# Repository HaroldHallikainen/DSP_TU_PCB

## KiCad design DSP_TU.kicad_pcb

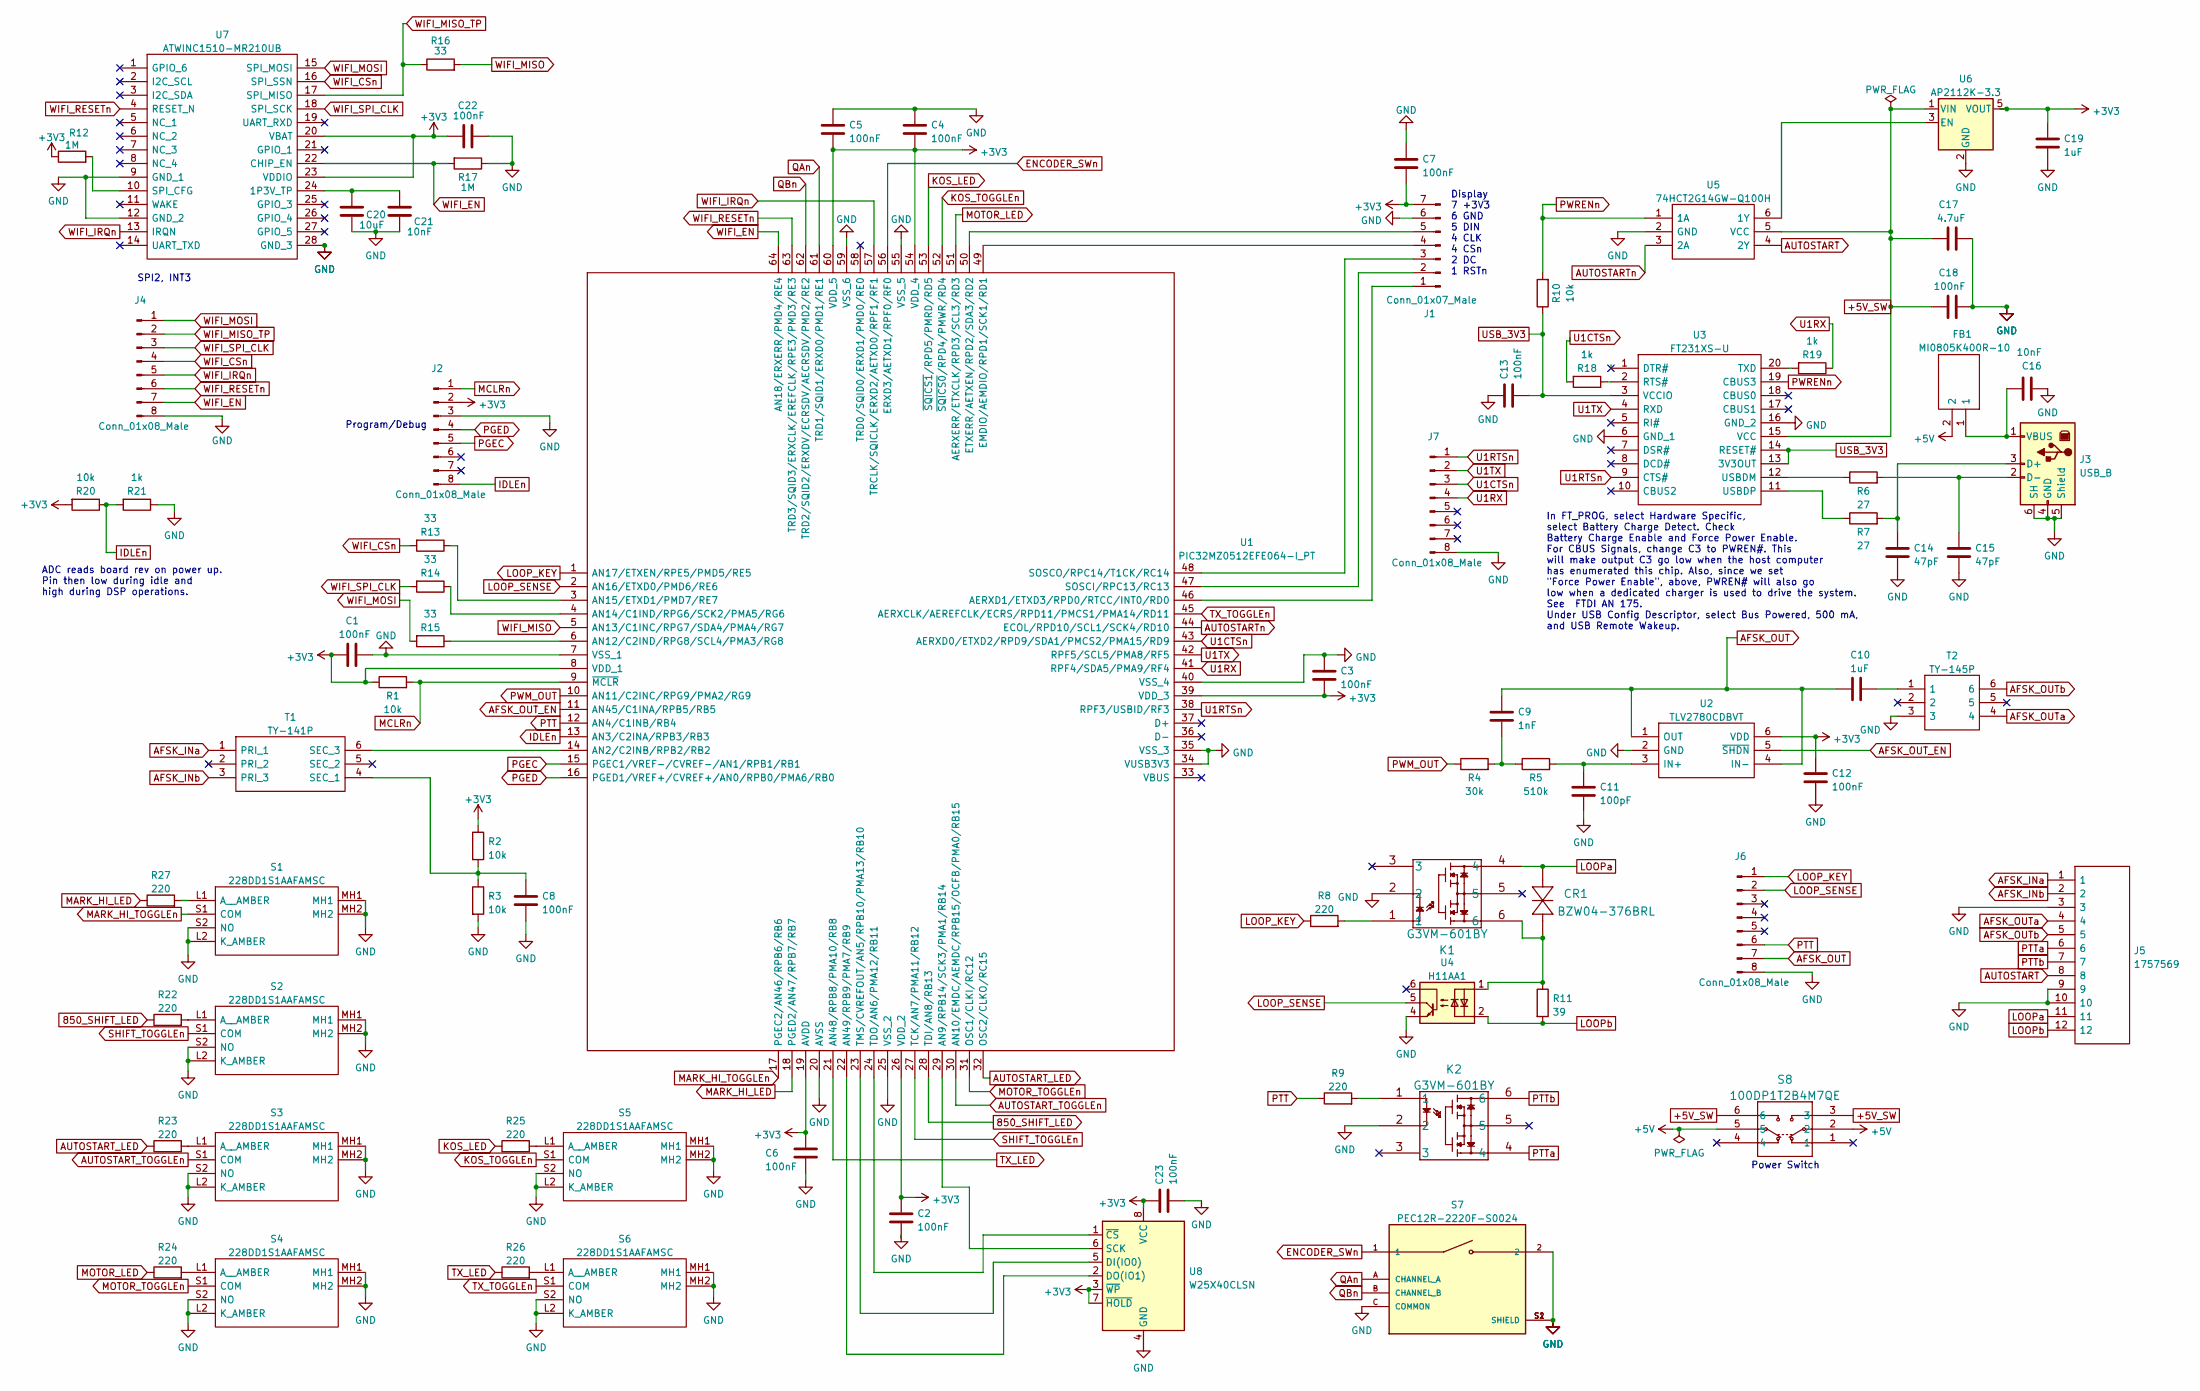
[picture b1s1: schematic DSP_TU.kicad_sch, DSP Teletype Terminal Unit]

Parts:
C1, C2, C3, C4, C5, C6, C7, C8, C12, C13, C18, C22, C23: 100nF; C_0603_1608Metric_Pad1.08x0.95mm_HandSolder
C9: 1nF; C_0603_1608Metric_Pad1.08x0.95mm_HandSolder
C10, C19: 1uF; C_0603_1608Metric_Pad1.08x0.95mm_HandSolder
C11: 100pF; C_0603_1608Metric_Pad1.08x0.95mm_HandSolder
C14, C15: 47pF; C_0603_1608Metric_Pad1.08x0.95mm_HandSolder
C16, C21: 10nF; C_0603_1608Metric_Pad1.08x0.95mm_HandSolder
C17: 4.7uF; C_0603_1608Metric_Pad1.08x0.95mm_HandSolder
C20: 10uF; C_0603_1608Metric_Pad1.08x0.95mm_HandSolder
CR1: BZW04-376BRL
FB1: MI0805K400R-10; BEADC2012X110N; Manufacturer_Part_Number MI0805K400R-10; Mouser Part Number 875-MI0805K400R-10
J1: Conn_01x07_Male; PinHeader_1x07_P2.54mm_Horizontal
J2, J4, J6, J7: Conn_01x08_Male; PinHeader_1x08_P2.54mm_Vertical
J3: USB_B; UJ2-BH-BL1-TH
J5: 1757569; Manufacturer_Part_Number 1757569; Mouser Part Number 651-1757569
K1, K2: G3VM-601BY; DIP-6_W7.62mm
R1, R2, R3, R10, R20: 10k; R_0603_1608Metric_Pad0.98x0.95mm_HandSolder
R4: 30k; R_0603_1608Metric_Pad0.98x0.95mm_HandSolder
R5: 510k; R_0603_1608Metric_Pad0.98x0.95mm_HandSolder
R6, R7: 27; R_0603_1608Metric_Pad0.98x0.95mm_HandSolder
R8, R9, R22, R23, R24, R25, R26, R27: 220; R_0603_1608Metric_Pad0.98x0.95mm_HandSolder
R11: 39; R_0603_1608Metric_Pad0.98x0.95mm_HandSolder
R12, R17: 1M; R_0603_1608Metric_Pad0.98x0.95mm_HandSolder
R13, R14, R15, R16: 33; R_0603_1608Metric_Pad0.98x0.95mm_HandSolder
R18, R19, R21: 1k; R_0603_1608Metric_Pad0.98x0.95mm_HandSolder
S1, S2, S3, S4, S5, S6: 228DD1S1AAFAMSC; Manufacturer_Part_Number 228DD1S1AAFAMSC; Mouser Part Number 774-228DD1S1AAFAMSC
S7: PEC12R-2220F-S0024; XDCR_PEC12R-2220F-S0024; PARTREV 07/21
S8: 100DP1T2B4M7QE; 100DP1T2B4M7QE_EWI
T1: TY-141P; DIPS1067W107P475L2062H1880Q6N; Manufacturer_Part_Number TY-141P; Mouser Part Number 553-TY141P
T2: TY-145P; DIPS1067W107P475L2062H1880Q6N; Manufacturer_Part_Number TY-145P; Mouser Part Number 553-TY145P
U1: PIC32MZ0512EFE064-I_PT; QFP50P1200X1200X120-64N; Manufacturer_Part_Number PIC32MZ0512EFE064-I/PT; Mouser Part Number 579-MZ0512EFE064IPT
U2: TLV2780CDBVT; SOT95P280X145-6N; Manufacturer_Part_Number TLV2780CDBVT; Mouser Part Number 595-TLV2780CDBVT
U3: FT231XS-U; SSOP-20_5.3x7.2mm_P0.65mm; Manufacturer_Part_Number FT231XS-U; Mouser Part Number 895-FT231XS-U
U4: H11AA1; DIP-6_W7.62mm
U5: 74HCT2G14GW-Q100H; 74HCT2G14GWQ100H; Manufacturer_Part_Number 74HCT2G14GW-Q100H; Mouser Part Number 771-74HCT2G14GWQ100H
U6: AP2112K-3.3; SOT-23-5
U7: ATWINC1510-MR210UB; ATWINC1510MR210UB; Mouser Part Number 556-ATWINC1510MR210U
U8: W25X40CLSN; SOIC-8_3.9x4.9mm_P1.27mm

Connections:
850_SHIFT_LED: R22.1, U1.28 (TDI/AN8/RB13)
+3V3: C1.2, C2.1, C3.2, C4.2, C5.2, C6.1, C7.2, C12.1, C19.1, C22.1, C23.1, J1.7, J2.2, R1.1, R2.1, R12.1, R20.2, U1.8 (VDD_1), U1.19 (AVDD), U1.26 (VDD_2), U1.39 (VDD_3), U1.54 (VDD_4), U1.60 (VDD_5), U2.6 (VDD), U6.5 (VOUT), U7.20 (VBAT), U7.23 (VDDIO), U8.3 (~WP), U8.7 (~HOLD), U8.8 (VCC)
+5V: FB1.2, S8.2, S8.5
+5V_SW: C17.1, C18.1, S8.3, S8.6, U3.15 (VCC), U5.5 (VCC), U6.1 (VIN)
AFSK_INa: J5.1, T1.1 (PRI_1)
AFSK_INb: J5.2, T1.3 (PRI_3)
AFSK_OUT: C9.1, C10.2, J6.7, U2.1 (OUT), U2.4 (IN-)
AFSK_OUT_EN: U1.11 (AN45/C1INA/RPB5/RB5), U2.5 (~SHDN)
AFSK_OUTa: J5.4, T2.4
AFSK_OUTb: J5.5, T2.6
AUTOSTART: J5.8, U5.4 (2Y)
AUTOSTART_LED: R23.1, U1.32 (OSC2/CLKO/RC15)
AUTOSTART_TOGGLEn: S3.S1 (COM), U1.30 (AN10/EMDC/AEMDC/RPB15/OCFB/PMA0/RB15)
AUTOSTARTn: U1.44 (ECOL/RPD10/SCL1/SCK4/RD10), U5.3 (2A)
ENCODER_SWn: S7.1, U1.56 (ERXD3/AETXD1/RPF0/RF0)
GND: C1.1, C2.2, C3.1, C4.1, C5.1, C6.2, C7.1, C8.2, C11.2, C12.2, C13.1, C14.2, C15.2, C16.2, C17.2, C18.2, C19.2, C20.2, C21.2, C22.2, C23.2, J1.6, J2.3, J3.4 (GND), J3.5 (Shield), J3.6 (SH), J4.8, J5.3, J5.9, J5.10, J6.8, J7.8, K1.2, K2.2, R3.2, R17.1, R21.1, S1.L2 (K_AMBER), S1.MH1, S1.MH2, S1.S2 (NO), S2.L2 (K_AMBER), S2.MH1, S2.MH2, S2.S2 (NO), S3.L2 (K_AMBER), S3.MH1, S3.MH2, S3.S2 (NO), S4.L2 (K_AMBER), S4.MH1, S4.MH2, S4.S2 (NO), S5.L2 (K_AMBER), S5.MH1, S5.MH2, S5.S2 (NO), S6.L2 (K_AMBER), S6.MH1, S6.MH2, S6.S2 (NO), S7.2, S7.C (COMMON), S7.S1 (SHIELD), S7.S2 (SHIELD), T2.3, U1.7 (VSS_1), U1.20 (AVSS), U1.25 (VSS_2), U1.34 (VUSB3V3), U1.35 (VSS_3), U1.40 (VSS_4), U1.55 (VSS_5), U1.59 (VSS_6), U2.2 (GND), U3.6 (GND_1), U3.16 (GND_2), U4.4, U5.2 (GND), U6.2 (GND), U7.9 (GND_1), U7.12 (GND_2), U7.28 (GND_3), U8.4 (GND)
IDLEn: J2.8, R20.1, R21.2, U1.13 (AN3/C2INA/RPB3/RB3)
KOS_LED: R25.1, U1.53 (~SQICS1/RPD5/PMRD/RD5)
KOS_TOGGLEn: S5.S1 (COM), U1.52 (~SQICS0/RPD4/PMWR/RD4)
LOOP_KEY: J6.1, R8.1, U1.1 (AN17/ETXEN/RPE5/PMD5/RE5)
LOOP_SENSE: J6.2, U1.2 (AN16/ETXD0/PMD6/RE6), U4.5
LOOPa: CR1.1 (CATHODE/ANODE), J5.11, K1.4
LOOPb: J5.12, R11.2, U4.2
MARK_HI_LED: R27.1, U1.18 (PGED2/AN47/RPB7/RB7)
MARK_HI_TOGGLEn: S1.S1 (COM), U1.17 (PGEC2/AN46/RPB6/RB6)
MCLRn: J2.1, R1.2, U1.9 (~MCLR)
MOTOR_LED: R24.1, U1.51 (AERXERR/ETXCLK/RPD3/SCL3/RD3)
MOTOR_TOGGLEn: S4.S1 (COM), U1.31 (OSC1/CLKI/RC12)
unnamed: C9.2, R4.2, R5.1
unnamed: C10.1, T2.1
unnamed: CR1.2 (CATHODE/ANODE), K1.6, R11.1, U4.1
unnamed: J1.1, U1.46 (AERXD1/ETXD3/RPD0/RTCC/INT0/RD0)
unnamed: J1.2, U1.47 (SOSCI/RPC13/RC13)
unnamed: J1.3, U1.48 (SOSCO/RPC14/T1CK/RC14)
unnamed: J1.4, U1.49 (EMDIO/AEMDIO/RPD1/SCK1/RD1)
unnamed: J1.5, U1.50 (ETXERR/AETXEN/RPD2/SDA3/RD2)
unnamed: C14.1, J3.3 (D+), R7.2
unnamed: C15.1, J3.2 (D-), R6.2
unnamed: C16.1, FB1.1, J3.1 (VBUS)
unnamed: K1.1, R8.2
unnamed: K2.1, R9.2
unnamed: R27.2, S1.L1 (A__AMBER)
unnamed: R22.2, S2.L1 (A__AMBER)
unnamed: R23.2, S3.L1 (A__AMBER)
unnamed: R24.2, S4.L1 (A__AMBER)
unnamed: R25.2, S5.L1 (A__AMBER)
unnamed: R26.2, S6.L1 (A__AMBER)
unnamed: C8.1, R2.2, R3.1, T1.4 (SEC_1)
unnamed: T1.6 (SEC_3), U1.14 (AN2/C2INB/RPB2/RB2)
unnamed: U1.29 (AN9/RPB14/SCK3/PMA1/RB14), U8.6 (SCK)
unnamed: R15.1, U1.6 (AN12/C2IND/RPG8/SCL4/PMA3/RG8)
unnamed: R14.1, U1.4 (AN14/C1IND/RPG6/SCK2/PMA5/RG6)
unnamed: R13.1, U1.3 (AN15/ETXD1/PMD7/RE7)
unnamed: U1.22 (AN49/RPB9/PMA7/RB9), U8.2 (DO(IO1))
unnamed: U1.24 (TDO/AN6/PMA12/RB11), U8.1 (~CS)
unnamed: U1.23 (TMS/CVREFOUT/AN5/RPB10/PMA13/RB10), U8.5 (DI(IO0))
unnamed: C11.1, R5.2, U2.3 (IN+)
unnamed: R18.1, U3.2 (RTS#)
unnamed: R19.2, U3.20 (TXD)
unnamed: R6.1, U3.12 (USBDM)
unnamed: R7.1, U3.11 (USBDP)
unnamed: U5.6 (1Y), U6.3 (EN)
unnamed: C20.1, C21.1, U7.24 (1P3V_TP)
unnamed: R12.2, U7.10 (SPI_CFG)
PGEC: J2.5, U1.15 (PGEC1/VREF-/CVREF-/AN1/RPB1/RB1)
PGED: J2.4, U1.16 (PGED1/VREF+/CVREF+/AN0/RPB0/PMA6/RB0)
PTT: J6.6, R9.1, U1.12 (AN4/C1INB/RB4)
PTTa: J5.6, K2.4
PTTb: J5.7, K2.6
PWM_OUT: R4.1, U1.10 (AN11/C2INC/RPG9/PMA2/RG9)
PWRENn: R10.2, U3.19 (CBUS3), U5.1 (1A)
QAn: S7.A (CHANNEL_A), U1.61 (TRD1/SQID1/ERXD0/PMD1/RE1)
QBn: S7.B (CHANNEL_B), U1.62 (TRD2/SQID2/ERXDV/ECRSDV/AECRSDV/PMD2/RE2)
SHIFT_TOGGLEn: S2.S1 (COM), U1.27 (TCK/AN7/PMA11/RB12)
TX_LED: R26.1, U1.21 (AN48/RPB8/PMA10/RB8)
TX_TOGGLEn: S6.S1 (COM), U1.45 (AERXCLK/AEREFCLK/ECRS/RPD11/PMCS1/PMA14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)
U1CTSn: J7.3, R18.2, U1.43 (AERXD0/ETXD2/RPD9/SDA1/PMCS2/PMA15/RD9)
U1RTSn: J7.1, U1.38 (RPF3/USBID/RF3), U3.9 (CTS#)
U1RX: J7.4, R19.1, U1.41 (RPF4/SDA5/PMA9/RF4)
U1TX: J7.2, U1.42 (RPF5/SCL5/PMA8/RF5), U3.4 (RXD)
USB_3V3: C13.2, R10.1, U3.3 (VCCIO), U3.13 (3V3OUT), U3.14 (RESET#)
WIFI_CSn: J4.4, R13.2, U7.16 (SPI_SSN)
WIFI_EN: J4.7, R17.2, U1.64 (AN18/ERXERR/PMD4/RE4), U7.22 (CHIP_EN)
WIFI_IRQn: J4.5, U1.57 (TRCLK/SQICLK/ERXD2/AETXD0/RPF1/RF1), U7.13 (IRQN)
WIFI_MISO: R16.2, U1.5 (AN13/C1INC/RPG7/SDA4/PMA4/RG7)
WIFI_MISO_TP: J4.2, R16.1, U7.17 (SPI_MISO)
WIFI_MOSI: J4.1, R15.2, U7.15 (SPI_MOSI)
WIFI_RESETn: J4.6, U1.63 (TRD3/SQID3/ERXCLK/EREFCLK/RPE3/PMD3/RE3), U7.4 (RESET_N)
WIFI_SPI_CLK: J4.3, R14.2, U7.18 (SPI_SCK)

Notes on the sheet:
Power Switch
SPI2, INT3
In FT_PROG, select Hardware Specific, select Battery Charge Detect. Check Battery Charge Enable and Force Power Enable. For CBUS Signals, change C3 to PWREN#. This will make output C3 go low when the host computer has enumerated this chip. Also, since we set "Force Power Enable", above, PWREN# will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
Display 7 +3V3 6 GND 5 DIN 4 CLK 4 CSn 2 DC 1 RSTn
ADC reads board rev on power up. Pin then low during idle and high during DSP operations.
Program/Debug

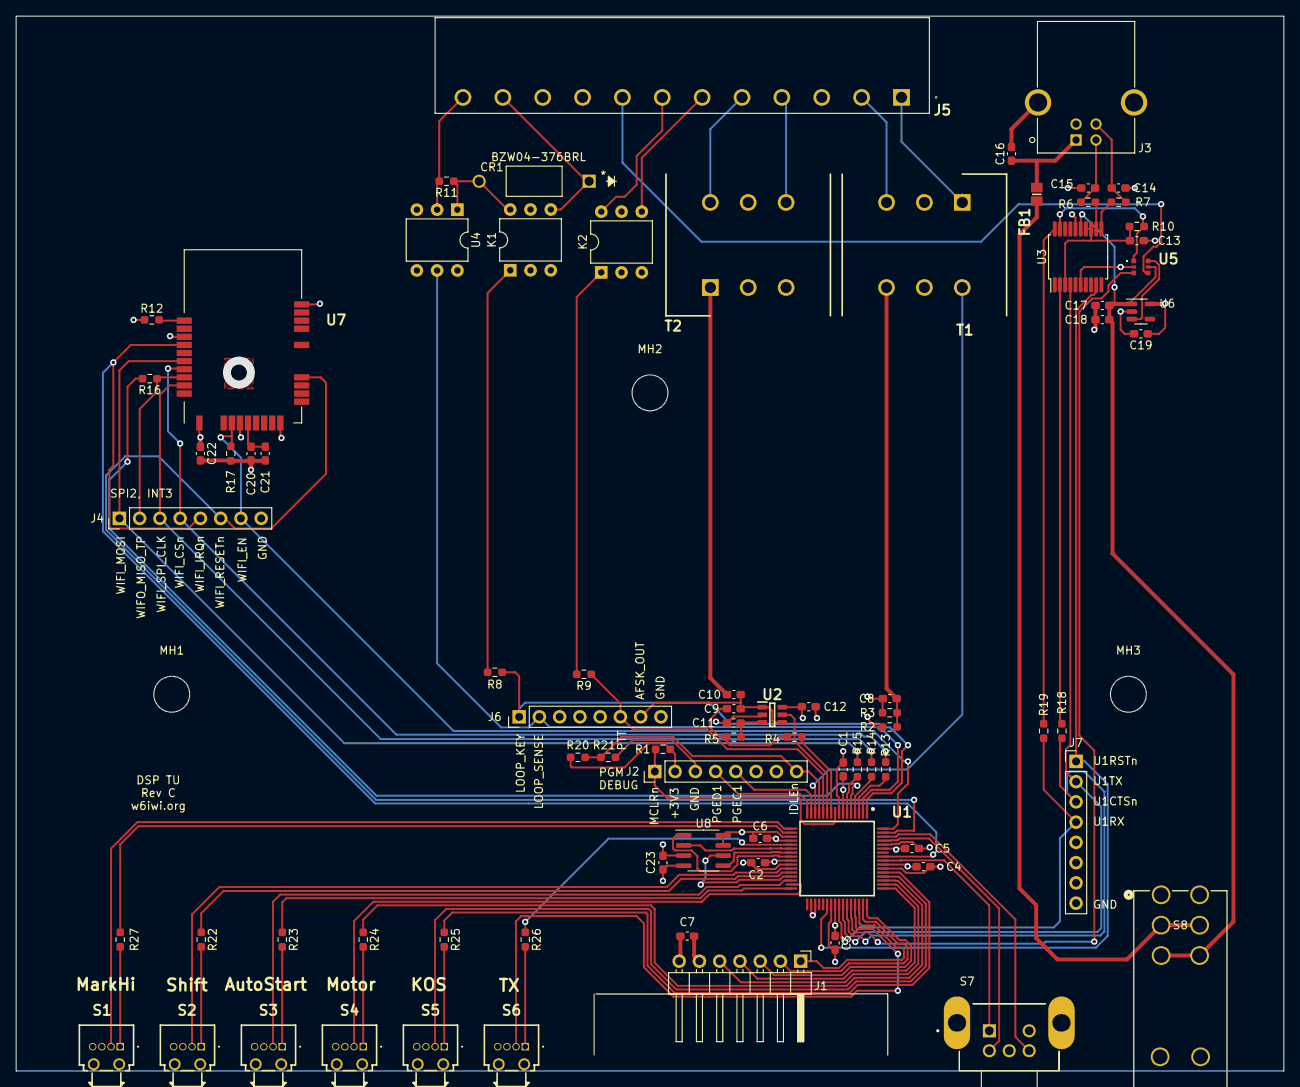
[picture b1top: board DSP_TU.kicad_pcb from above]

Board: 4 copper layers, 159.0 x 132.3 mm, 82 parts (0 on the bottom side), 89 nets.

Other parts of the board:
MH1, MH2, MH3: MountingHole_4.5mm

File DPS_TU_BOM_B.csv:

"Reference","Value","Datasheet","Footprint","Qty","DNP"
"C1,C2,C3,C4,C5,C6,C7,C8,C12,C13,C18,C22,C23","100nF","~","Capacitor_SMD:C_0603_1608Metric_Pad1.08x0.95mm_HandSolder","13",""
"C9","1nF","~","Capacitor_SMD:C_0603_1608Metric_Pad1.08x0.95mm_HandSolder","1",""
"C10,C19","1uF","~","Capacitor_SMD:C_0603_1608Metric_Pad1.08x0.95mm_HandSolder","2",""
"C11","100pF","~","Capacitor_SMD:C_0603_1608Metric_Pad1.08x0.95mm_HandSolder","1",""
"C14,C15","47pF","~","Capacitor_SMD:C_0603_1608Metric_Pad1.08x0.95mm_HandSolder","2",""
"C16,C21","10nF","~","Capacitor_SMD:C_0603_1608Metric_Pad1.08x0.95mm_HandSolder","2",""
"C17","4.7uF","~","Capacitor_SMD:C_0603_1608Metric_Pad1.08x0.95mm_HandSolder","1",""
"C20","10uF","~","Capacitor_SMD:C_0603_1608Metric_Pad1.08x0.95mm_HandSolder","1",""
"CR1","BZW04-376BRL","","HhLibrary:BZW04-376BRL","1",""
"FB1","MI0805K400R-10","https://assets.lairdtech.com/home/brandworld/files/MI0805K40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","HhLibrary:BEADC2012X110N","1",""
"J1","Conn_01x07_Male","~","Connector_PinHeader_2.54mm:PinHeader_1x07_P2.54mm_Horizontal","1",""
"J2,J4,J6,J7","Conn_01x08_Male","~","Connector_PinHeader_2.54mm:PinHeader_1x08_P2.54mm_Vertical","4",""
"J3","USB_B"," ~","HhLibrary:UJ2-BH-BL1-TH","1",""
"J5","1757569","http://www.phoenixcontact.com/de/produkte/1757569/pdf","HhLibrary:1757569","1",""
"K1,K2","G3VM-601BY","","Package_DIP:DIP-6_W7.62mm","2",""
"R1,R2,R3,R10,R20","10k","~","Resistor_SMD:R_0603_1608Metric_Pad0.98x0.95mm_HandSolder","5",""
"R4","30k","~","Resistor_SMD:R_0603_1608Metric_Pad0.98x0.95mm_HandSolder","1",""
"R5","510k","~","Resistor_SMD:R_0603_1608Metric_Pad0.98x0.95mm_HandSolder","1",""
"R6,R7","27","~","Resistor_SMD:R_0603_1608Metric_Pad0.98x0.95mm_HandSolder","2",""
"R8,R9,R22,R23,R24,R25,R26,R27","220","~","Resistor_SMD:R_0603_1608Metric_Pad0.98x0.95mm_HandSolder","8",""
"R11","39","~","Resistor_SMD:R_0603_1608Metric_Pad0.98x0.95mm_HandSolder","1",""
"R12,R17","1M","~","Resistor_SMD:R_0603_1608Metric_Pad0.98x0.95mm_HandSolder","2",""
"R13,R14,R15,R16","33","~","Resistor_SMD:R_0603_1608Metric_Pad0.98x0.95mm_HandSolder","4",""
"R18,R19,R21","1k","~","Resistor_SMD:R_0603_1608Metric_Pad0.98x0.95mm_HandSolder","3",""
"S1,S2,S3,S4,S5,S6","228DD1S1AAFAMSC","https://www.ctscorp.com/wp-content/uploads/228D.pdf","228DD1S1AAFAMSC","6",""
"S7","PEC12R-2220F-S0024","","XDCR_PEC12R-2220F-S0024","1",""
"S8","100DP1T2B4M7QE","100DP1T2B4M7QE","100DP1T2B4M7QE_EWI","1",""
"T1","TY-141P","http://catalog.triadmagnetics.com/Asset/TY-141P.pdf","HhLibrary:DIPS1067W107P475L2062H1880Q6N","1",""
"T2","TY-145P","https://catalog.triadmagnetics.com/Asset/TY-145P.pdf","HhLibrary:DIPS1067W107P475L2062H1880Q6N","1",""
"U1","PIC32MZ0512EFE064-I_PT","http://www.mouser.com/ds/2/268/60001320D-967555.pdf","HhLibrary:QFP50P1200X1200X120-64N","1",""
"U2","TLV2780CDBVT","https://www.ti.com/general/docs/suppproductinfo.tsp?distId=2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","HhLibrary:SOT95P280X145-6N","1",""
"U3","FT231XS-U","https://www.ftdichip.com/Support/Documents/DataSheets/ICs/DS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","Package_SO:SSOP-20_5.3x7.2mm_P0.65mm","1",""
"U4","H11AA1","https://www.vishay.com/docs/83608/h11aa1.pdf","Package_DIP:DIP-6_W7.62mm","1",""
"U5","74HCT2G14GW-Q100H","https://assets.nexperia.com/documents/data-sheet/74HC_HCT2G1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","HhLibrary:74HCT2G14GWQ100H","1",""
"U6","AP2112K-3.3","https://www.diodes.com/assets/Datasheets/AP2112.pdf","Package_TO_SOT_SMD:SOT-23-5","1",""
"U7","ATWINC1510-MR210UB","http://ww1.microchip.com/downloads/en/DeviceDoc/70005304B.pdf","HhLibrary:ATWINC1510MR210UB","1",""
"U8","W25X40CLSN","https://www.winbond.com/resource-files/W25X40CL_G%2020210505.pdf","Package_SO:SOIC-8_3.9x4.9mm_P1.27mm","1",""

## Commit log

2023-09-10 PCB rev A
2024-07-12 PCB Rev B, changing dimensions, adding test points, adding resistors in UART lines, and correcting display pinout. hh
2024-07-12 PCB rev B
2024-07-12 Added rev B schematic PDF
2025-07-10 Update all to rev C

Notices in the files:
parts and their libraries:
Copyright 2021 Accelerated Designs. All rights reserved.
